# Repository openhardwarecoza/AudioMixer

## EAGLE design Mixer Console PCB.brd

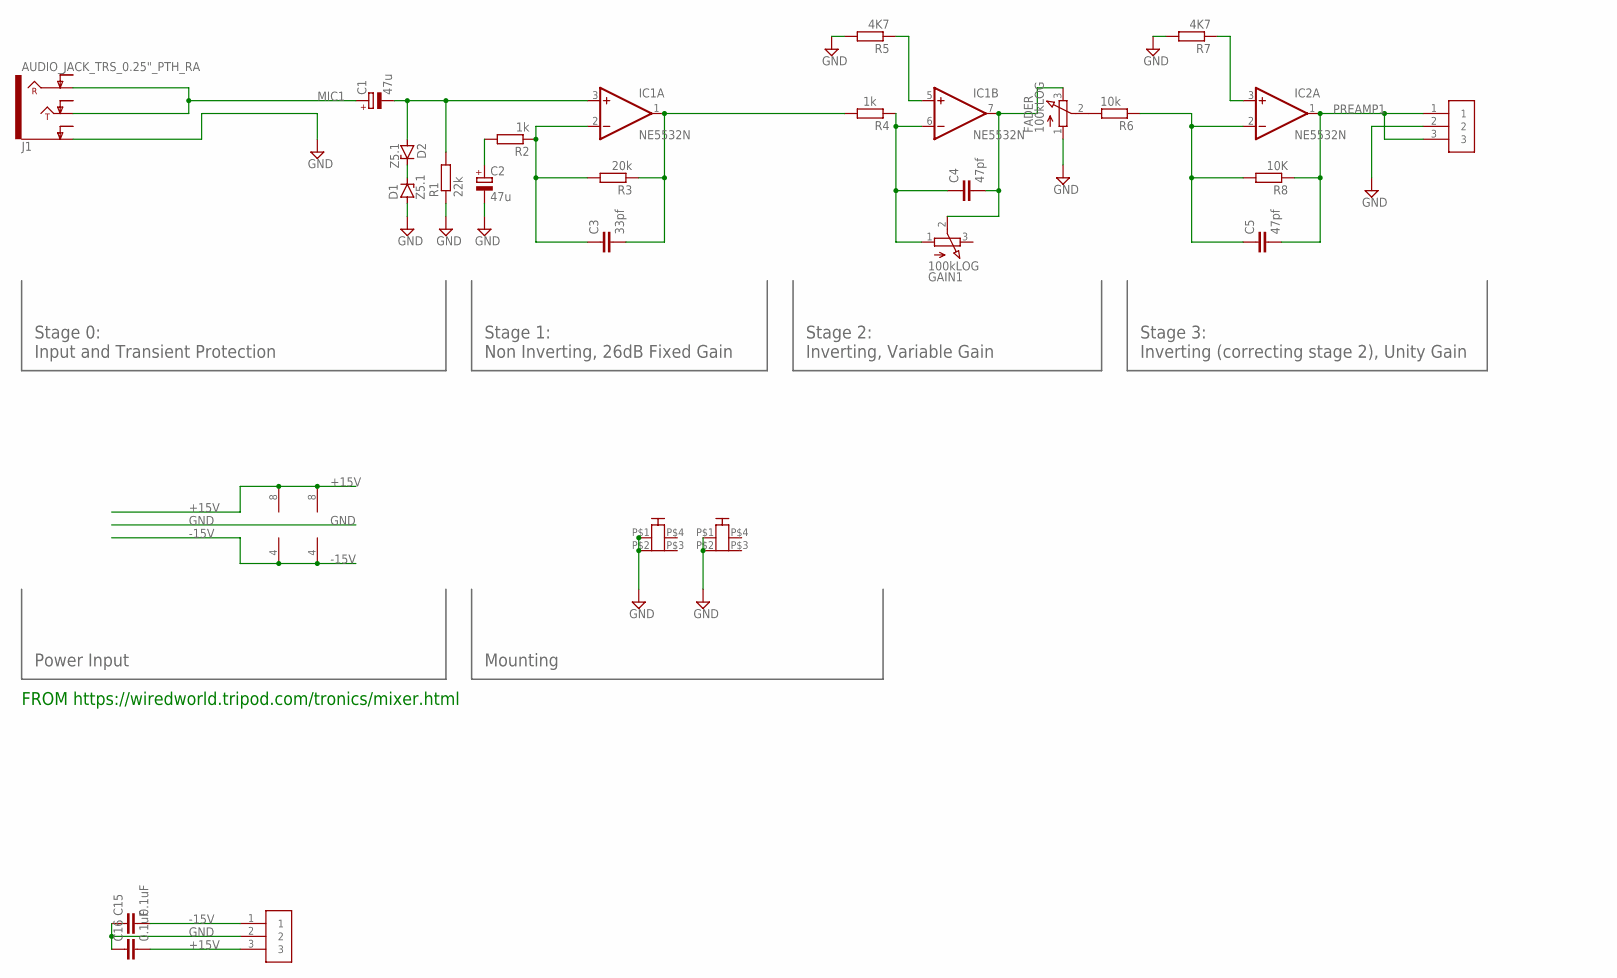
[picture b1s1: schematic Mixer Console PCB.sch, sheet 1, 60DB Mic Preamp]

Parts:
C1, C2: 47u; E5-6
C3: 33pf; C2.5-2
C4, C5: 47pf; C2.5-2
C15, C16: 0.1uF; C2.5-2
CON11, CON12: PCB-2M3; PCB2-M3
D1, D2: Z5.1; DO34Z7
FADER: 100kLOG; 3RP/1610N
GAIN1: 100kLOG; 3RP/1610N
IC1, IC2: NE5532N; DIL08
J1: AUDIO_JACK_TRS_0.25"_PTH_RA; AUDIO_JACK_0.25"_TRS_PTH_RA
PREAMPOUT: Phoenix Pluggable 3.81mm 3 way; 3.81MM-3WAY-PLUGGABLE-SCREW
PWRIN: Phoenix Pluggable 3.81mm 3 way; 3.81MM-3WAY-PLUGGABLE-SCREW
R1: 22k; 0204/7
R2, R4: 1k; 0204/7
R3: 20k; 0204/7
R5, R7: 4K7; 0204/7
R6: 10k; 0204/7
R8: 10K; 0204/7

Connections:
+15V: C16.2, IC1.8 (V+), IC2.8 (V+), PWRIN.3; also elsewhere on the board
-15V: C15.2, IC1.4 (V-), IC2.4 (V-), PWRIN.1; also elsewhere on the board
GND: C2.-, C15.1, C16.1, CON11.P$1, CON11.P$2, CON12.P$1, CON12.P$2, D1.A, FADER.1 (A), J1.SLEEVE (EARTH), PREAMPOUT.2, PWRIN.2, R1.1, R5.2, R7.2; also elsewhere on the board
MIC1: C1.+, J1.RING, J1.TIP
unnamed: C1.-, D2.A, IC1.3 (+IN), R1.2
unnamed: C2.+, R2.2
unnamed: C3.1, IC1.2 (-IN), R2.1, R3.2
unnamed: C3.2, IC1.1 (OUT), R3.1, R4.2
unnamed: C4.1, GAIN1.1 (A), IC1.6 (-IN), R4.1
unnamed: IC1.5 (+IN), R5.1
unnamed: C4.2, FADER.3 (E), GAIN1.2 (S), IC1.7 (OUT)
unnamed: IC2.3 (+IN), R7.1
unnamed: D1.C, D2.C
unnamed: C5.1, IC2.2 (-IN), R6.1, R8.2
unnamed: FADER.2 (S), R6.2
PREAMP1: C5.2, IC2.1 (OUT), PREAMPOUT.1, PREAMPOUT.3, R8.1

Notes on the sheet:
FROM https://wiredworld.tripod.com/tronics/mixer.html
Stage 1: Non Inverting, 26dB Fixed Gain
Stage 2: Inverting, Variable Gain
Stage 3: Inverting (correcting stage 2), Unity Gain
Stage 0: Input and Transient Protection
Power Input
Mounting

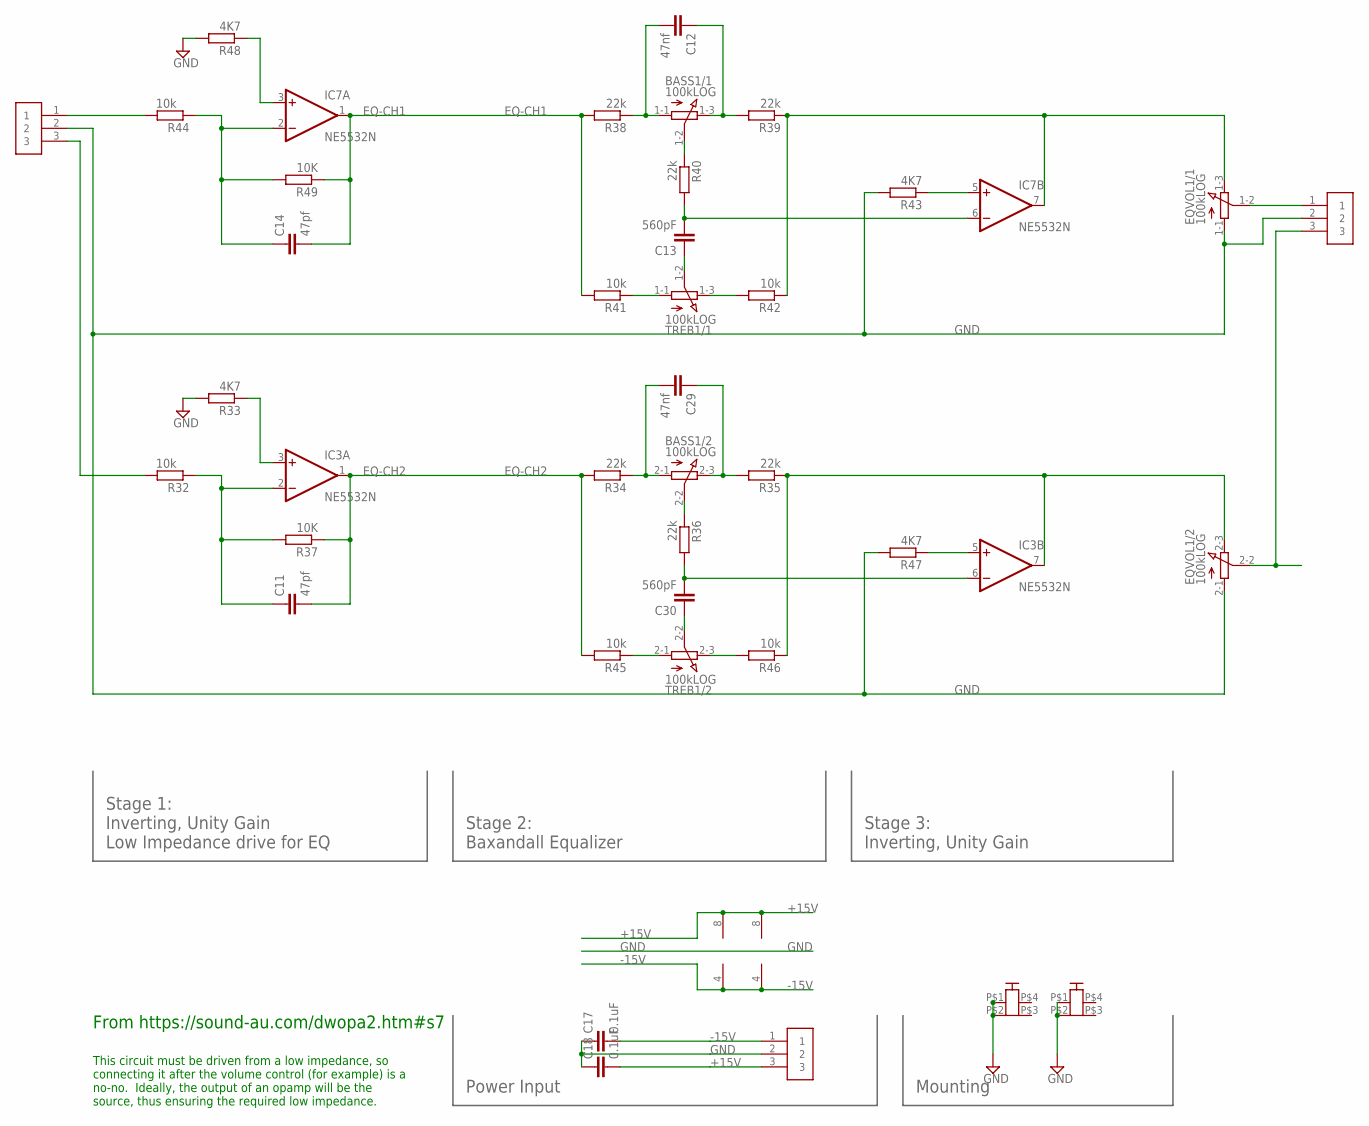
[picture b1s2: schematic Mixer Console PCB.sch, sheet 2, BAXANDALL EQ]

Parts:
BASS1: 100kLOG; 3RP/1610G
C11, C14: 47pf; C2.5-2
C12, C29: 47nf; C2.5-2
C13, C30: 560pF; C2.5-2
C17, C18: 0.1uF; C2.5-2
CON1, CON2: PCB-2M3; PCB2-M3
EQIN: Phoenix Pluggable 3.81mm 3 way; 3.81MM-3WAY-PLUGGABLE-SCREW
EQOUT: Phoenix Pluggable 3.81mm 3 way; 3.81MM-3WAY-PLUGGABLE-SCREW
EQVOL1: 100kLOG; 3RP/1610G
IC3, IC7: NE5532N; DIL08
PWRIN1: Phoenix Pluggable 3.81mm 3 way; 3.81MM-3WAY-PLUGGABLE-SCREW
R32, R41, R42, R44, R45, R46: 10k; 0204/7
R33, R43, R47, R48: 4K7; 0204/7
R34, R35, R36, R38, R39, R40: 22k; 0204/7
R37, R49: 10K; 0204/7
TREB1: 100kLOG; 3RP/1610G

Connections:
+15V: C18.2, IC3.8 (V+), IC7.8 (V+), PWRIN1.3; also elsewhere on the board
-15V: C17.2, IC3.4 (V-), IC7.4 (V-), PWRIN1.1; also elsewhere on the board
EQ-CH1: C14.2, IC7.1 (OUT), R38.2, R41.2, R49.1
EQ-CH2: C11.2, IC3.1 (OUT), R34.2, R37.1, R45.2
GND: C17.1, C18.1, CON1.P$1, CON1.P$2, CON2.P$1, CON2.P$2, EQIN.2, EQOUT.2, EQVOL1.1-1 (A), EQVOL1.2-1 (A), PWRIN1.2, R33.2, R43.2, R47.2, R48.2; also elsewhere on the board
unnamed: EQOUT.3, EQVOL1.2-2 (S)
unnamed: IC3.3 (+IN), R33.1
unnamed: C11.1, IC3.2 (-IN), R32.1, R37.2
unnamed: EQIN.3, R32.2
unnamed: BASS1.1-1 (A), C12.2, R38.1
unnamed: BASS1.1-3 (E), C12.1, R39.2
unnamed: BASS1.2-1 (A), C29.2, R34.1
unnamed: BASS1.2-3 (E), C29.1, R35.2
unnamed: BASS1.1-2 (S), R40.1
unnamed: BASS1.2-2 (S), R36.1
unnamed: C13.2, IC7.6 (-IN), R40.2
unnamed: C13.1, TREB1.1-2 (S)
unnamed: C30.2, IC3.6 (-IN), R36.2
unnamed: EQVOL1.1-3 (E), IC7.7 (OUT), R39.1, R42.1
unnamed: R42.2, TREB1.1-3 (E)
unnamed: C30.1, TREB1.2-2 (S)
unnamed: R41.1, TREB1.1-1 (A)
unnamed: IC7.5 (+IN), R43.1
unnamed: EQVOL1.2-3 (E), IC3.7 (OUT), R35.1, R46.1
unnamed: EQOUT.1, EQVOL1.1-2 (S)
unnamed: R46.2, TREB1.2-3 (E)
unnamed: R45.1, TREB1.2-1 (A)
unnamed: IC7.3 (+IN), R48.1
unnamed: C14.1, IC7.2 (-IN), R44.1, R49.2
unnamed: EQIN.1, R44.2
unnamed: IC3.5 (+IN), R47.1

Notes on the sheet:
Power Input
Mounting
Stage 2: Baxandall Equalizer
From https://sound-au.com/dwopa2.htm#s7
This circuit must be driven from a low impedance, so connecting it after the volume control (for example) is a no-no. Ideally, the output of an opamp will be the source, thus ensuring the required low impedance.
Stage 1: Inverting, Unity Gain Low Impedance drive for EQ
Stage 3: Inverting, Unity Gain

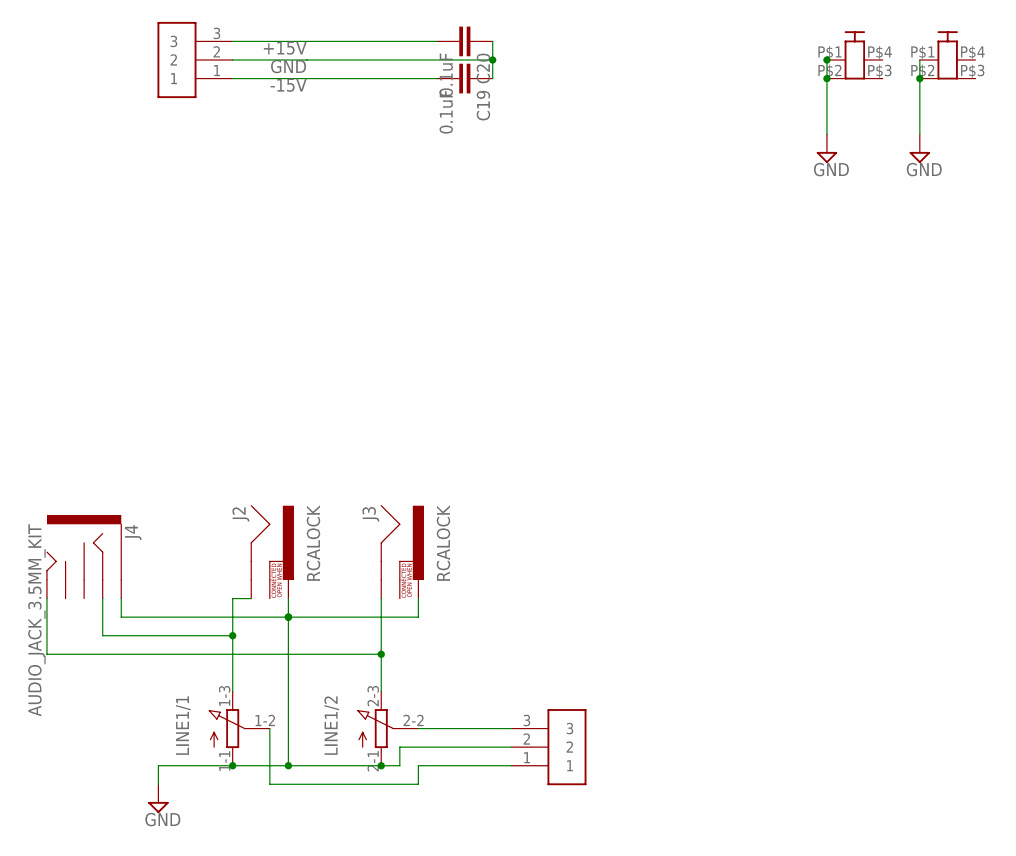
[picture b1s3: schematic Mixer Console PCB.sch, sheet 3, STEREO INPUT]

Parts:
C19, C20: 0.1uF; C2.5-2
CON3, CON4: PCB-2M3; PCB2-M3
J2, J3: RCALOCK; RCA_LOCK
J4: AUDIO_JACK_3.5MM_KIT; AUDIO-JACK-KIT
LINE1: 3RP/1610G
LINEIN-OUT: Phoenix Pluggable 3.81mm 3 way; 3.81MM-3WAY-PLUGGABLE-SCREW
PWRIN2: Phoenix Pluggable 3.81mm 3 way; 3.81MM-3WAY-PLUGGABLE-SCREW

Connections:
+15V: C20.2, PWRIN2.3; also elsewhere on the board
-15V: C19.2, PWRIN2.1; also elsewhere on the board
GND: C19.1, C20.1, CON3.P$1, CON3.P$2, CON4.P$1, CON4.P$2, J2.PIN, J3.PIN, J4.SLEEVE, LINE1.1-1 (A), LINE1.2-1 (A), LINEIN-OUT.2, PWRIN2.2; also elsewhere on the board
unnamed: LINE1.2-2 (S), LINEIN-OUT.3
unnamed: LINE1.1-2 (S), LINEIN-OUT.1
unnamed: J2.SHELL, J4.RING, LINE1.1-3 (E)
unnamed: J3.SHELL, J4.TIP, LINE1.2-3 (E)

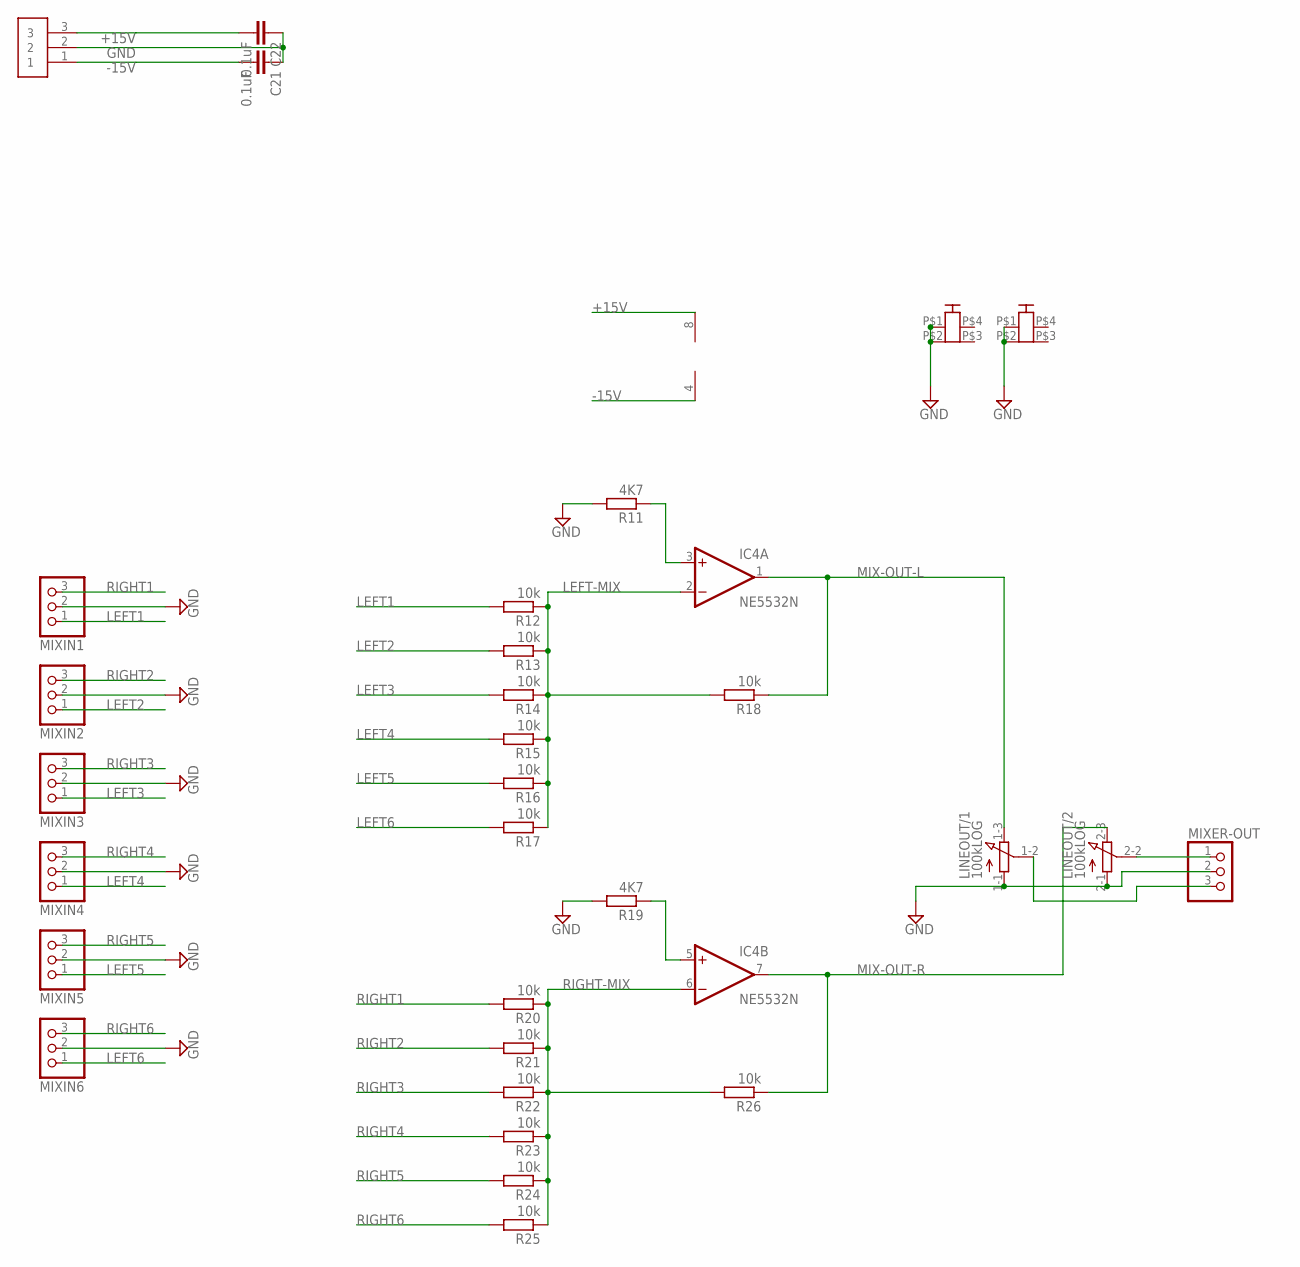
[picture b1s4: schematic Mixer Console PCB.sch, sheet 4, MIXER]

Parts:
C21, C22: 0.1uF; C2.5-2
CON5, CON6: PCB-2M3; PCB2-M3
IC4: NE5532N; DIL08
LINEOUT: 100kLOG; 3RP/1610G
MIXER-OUT: PINHD-1X3/90; 1X03/90
MIXIN1, MIXIN2, MIXIN3, MIXIN4, MIXIN5, MIXIN6: PINHD-1X3/90; 1X03/90
PWRIN3: Phoenix Pluggable 3.81mm 3 way; 3.81MM-3WAY-PLUGGABLE-SCREW
R11, R19: 4K7; 0204/7
R12, R13, R14, R15, R16, R17, R18, R20, R21, R22, R23, R24, R25, R26: 10k; 0204/7

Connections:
+15V: C22.2, IC4.8 (V+), PWRIN3.3; also elsewhere on the board
-15V: C21.2, IC4.4 (V-), PWRIN3.1; also elsewhere on the board
GND: C21.1, C22.1, CON5.P$1, CON5.P$2, CON6.P$1, CON6.P$2, LINEOUT.1-1 (A), LINEOUT.2-1 (A), MIXER-OUT.2, MIXIN1.2, MIXIN2.2, MIXIN3.2, MIXIN4.2, MIXIN5.2, MIXIN6.2, PWRIN3.2, R11.2, R19.2; also elsewhere on the board
LEFT1: MIXIN1.1, R12.2
LEFT2: MIXIN2.1, R13.2
LEFT3: MIXIN3.1, R14.2
LEFT4: MIXIN4.1, R15.2
LEFT5: MIXIN5.1, R16.2
LEFT6: MIXIN6.1, R17.2
LEFT-MIX: IC4.2 (-IN), R12.1, R13.1, R14.1, R15.1, R16.1, R17.1, R18.2
MIX-OUT-L: IC4.1 (OUT), LINEOUT.1-3 (E), R18.1
MIX-OUT-R: IC4.7 (OUT), LINEOUT.2-3 (E), R26.1
unnamed: IC4.5 (+IN), R19.1
unnamed: IC4.3 (+IN), R11.1
unnamed: LINEOUT.2-2 (S), MIXER-OUT.1
unnamed: LINEOUT.1-2 (S), MIXER-OUT.3
RIGHT1: MIXIN1.3, R20.2
RIGHT2: MIXIN2.3, R21.2
RIGHT3: MIXIN3.3, R22.2
RIGHT4: MIXIN4.3, R23.2
RIGHT5: MIXIN5.3, R24.2
RIGHT6: MIXIN6.3, R25.2
RIGHT-MIX: IC4.6 (-IN), R20.1, R21.1, R22.1, R23.1, R24.1, R25.1, R26.2

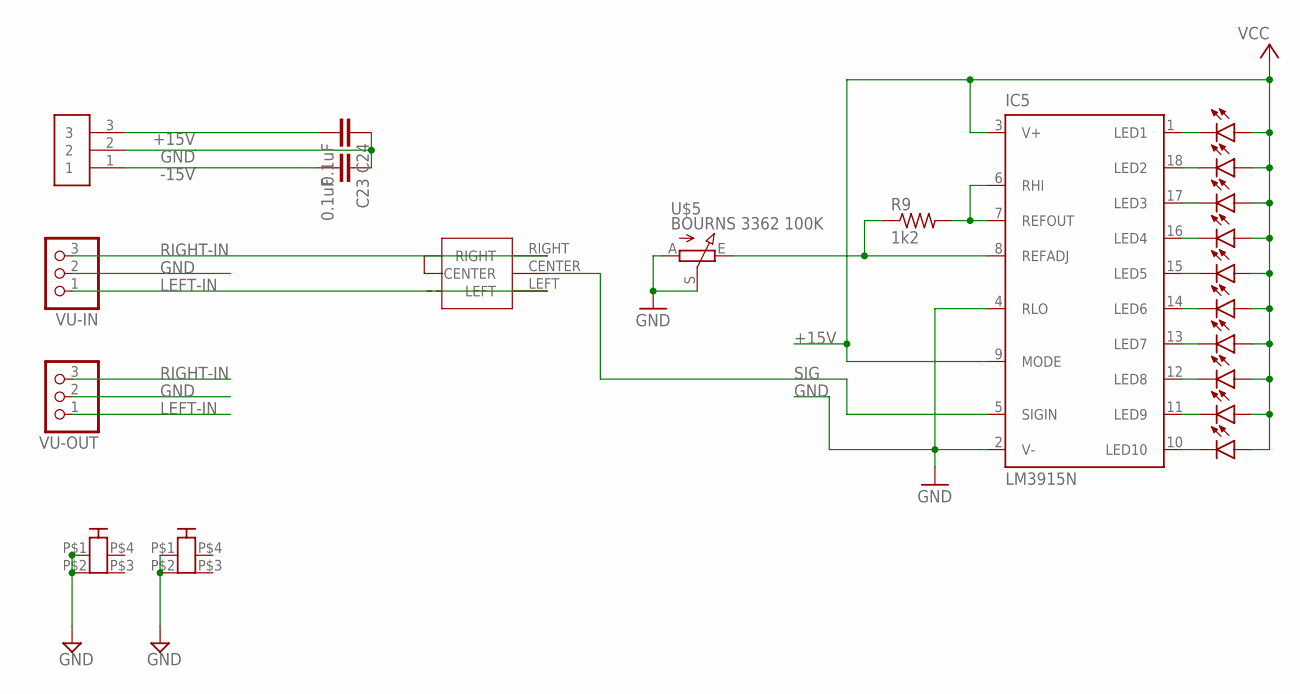
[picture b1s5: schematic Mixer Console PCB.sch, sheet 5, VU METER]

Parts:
C23, C24: 0.1uF; C2.5-2
CON7, CON8: PCB-2M3; PCB2-M3
IC5: LM3915N; DIL18
LED1, LED2, LED3, LED4, LED5, LED6, LED7, LED8, LED9, LED10: LED3MM
PWRIN4: Phoenix Pluggable 3.81mm 3 way; 3.81MM-3WAY-PLUGGABLE-SCREW
R9: 1k2; 0207/10
U$2: XKBENTERPRISESS-12D11G5R
U$5: BOURNS 3362 100K; POT_B64W
VU-IN: PINHD-1X3/90; 1X03/90
VU-OUT: PINHD-1X3/90; 1X03/90

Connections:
+15V: C24.2, IC5.3 (V+), IC5.9 (MODE), LED1.A, LED2.A, LED3.A, LED4.A, LED5.A, LED6.A, LED7.A, LED8.A, LED9.A, LED10.A, PWRIN4.3; also elsewhere on the board
-15V: C23.2, PWRIN4.1; also elsewhere on the board
GND: C23.1, C24.1, CON7.P$1, CON7.P$2, CON8.P$1, CON8.P$2, IC5.2 (V-), IC5.4 (RLO), PWRIN4.2, U$5.A, U$5.S, VU-IN.2, VU-OUT.2; also elsewhere on the board
LEFT-IN: U$2.LEFT, VU-IN.1, VU-OUT.1
unnamed: IC5.6 (RHI), IC5.7 (REFOUT), R9.2
unnamed: IC5.1 (LED1), LED1.K (C)
unnamed: IC5.18 (LED2), LED2.K (C)
unnamed: IC5.17 (LED3), LED3.K (C)
unnamed: IC5.16 (LED4), LED4.K (C)
unnamed: IC5.15 (LED5), LED5.K (C)
unnamed: IC5.14 (LED6), LED6.K (C)
unnamed: IC5.13 (LED7), LED7.K (C)
unnamed: IC5.12 (LED8), LED8.K (C)
unnamed: IC5.11 (LED9), LED9.K (C)
unnamed: IC5.10 (LED10), LED10.K (C)
REF: IC5.8 (REFADJ), R9.1, U$5.E
RIGHT-IN: U$2.RIGHT, VU-IN.3, VU-OUT.3
SIG: IC5.5 (SIGIN), U$2.CENTER

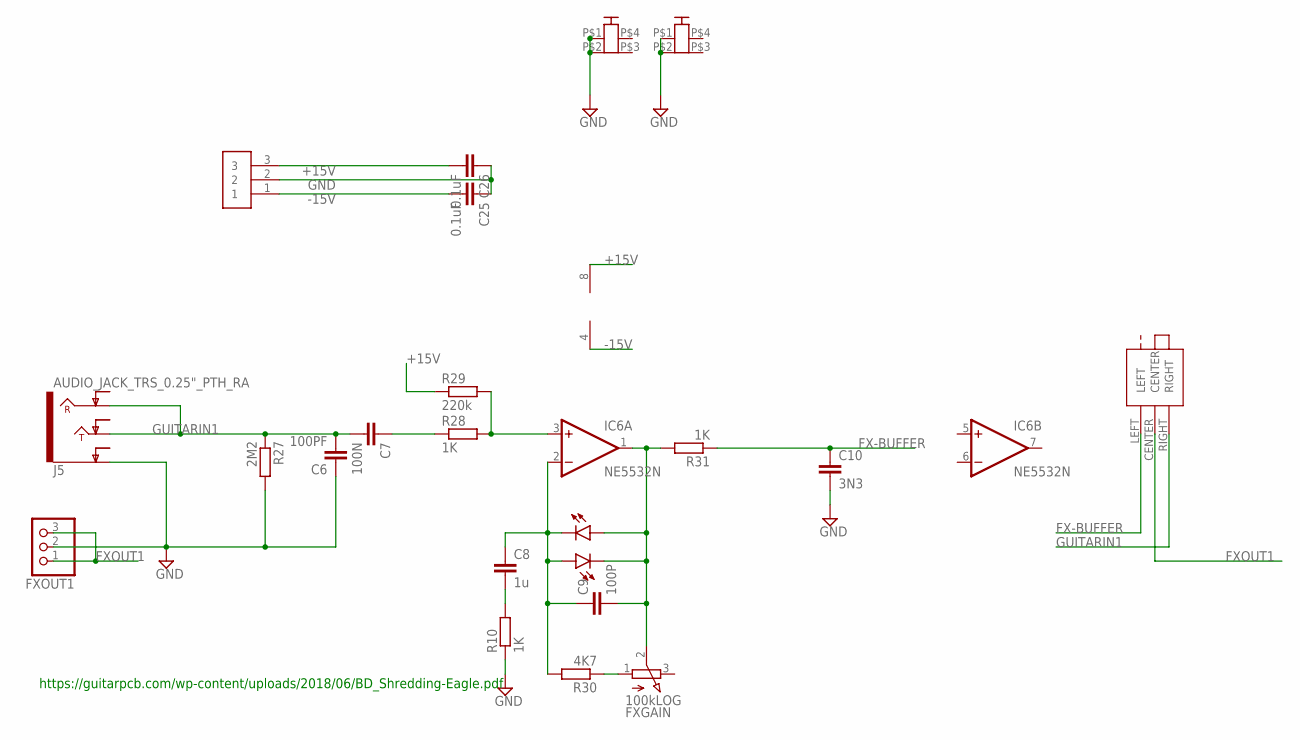
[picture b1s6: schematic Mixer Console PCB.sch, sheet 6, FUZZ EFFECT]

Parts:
C6: 100PF; C2.5-2
C7: 100N; C2.5-2
C8: 1u; C2.5-2
C9: 100P; C2.5-2
C10: 3N3; C2.5-2
C25, C26: 0.1uF; C2.5-2
CON9, CON10: PCB-2M3; PCB2-M3
FXGAIN: 100kLOG; 3RP/1610N
FXOUT1: PINHD-1X3/90; 1X03/90
IC6: NE5532N; DIL08
J5: AUDIO_JACK_TRS_0.25"_PTH_RA; AUDIO_JACK_0.25"_TRS_PTH_RA
LED11, LED12: LED3MM
PWRIN5: Phoenix Pluggable 3.81mm 3 way; 3.81MM-3WAY-PLUGGABLE-SCREW
R10, R28, R31: 1K; 0204/7
R27: 2M2; 0204/7
R29: 220k; 0204/7
R30: 4K7; 0204/7
U$1: XKBENTERPRISESS-12D11G5R

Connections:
+15V: C26.2, IC6.8 (V+), PWRIN5.3, R29.1; also elsewhere on the board
-15V: C25.2, IC6.4 (V-), PWRIN5.1; also elsewhere on the board
FX-BUFFER: C10.1, R31.1, U$1.LEFT
FXOUT1: FXOUT1.1, FXOUT1.3, U$1.CENTER
GND: C6.1, C10.2, C25.1, C26.1, CON9.P$1, CON9.P$2, CON10.P$1, CON10.P$2, FXOUT1.2, J5.SLEEVE (EARTH), PWRIN5.2, R10.1, R27.2; also elsewhere on the board
GUITARIN1: C6.2, C7.2, J5.RING, J5.TIP, R27.1, U$1.RIGHT
unnamed: IC6.3 (+IN), R28.2, R29.2
unnamed: C7.1, R28.1
unnamed: C8.1, C9.1, IC6.2 (-IN), LED11.K (C), LED12.A, R30.2
unnamed: C9.2, FXGAIN.2 (S), IC6.1 (OUT), LED11.A, LED12.K (C), R31.2
unnamed: C8.2, R10.2
unnamed: FXGAIN.1 (A), R30.1

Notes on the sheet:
https://guitarpcb.com/wp-content/uploads/2018/06/BD_Shredding-Eagle.pdf

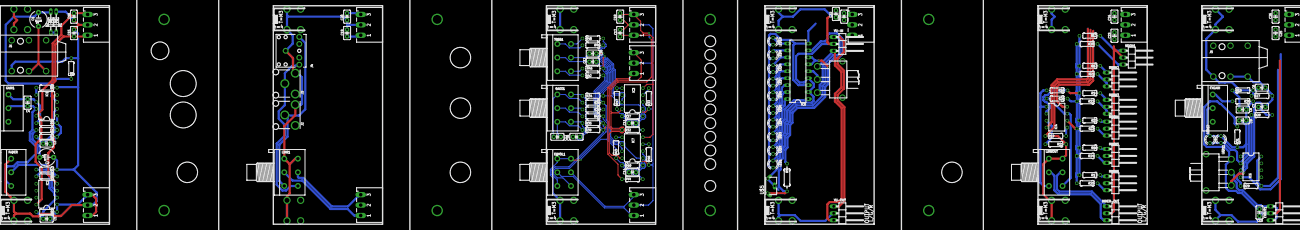
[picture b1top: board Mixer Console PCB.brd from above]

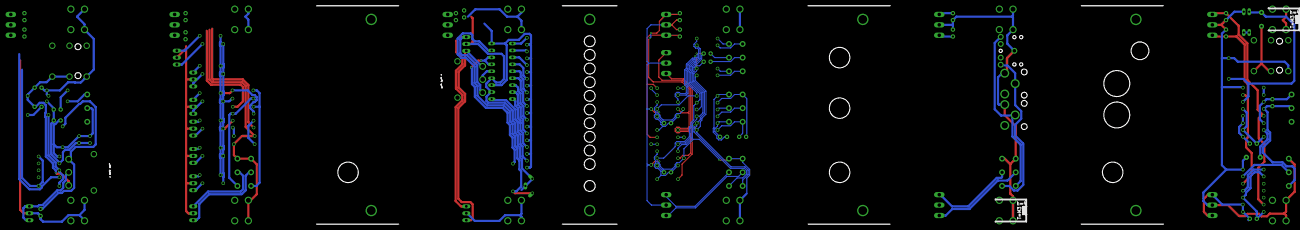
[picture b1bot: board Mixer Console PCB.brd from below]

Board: 2 copper layers, 146 parts (2 on the bottom side), 92 nets.

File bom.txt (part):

Partlist

Exported from Mixer Console PCB.brd at 2021/04/04 20:23

EAGLE Version 9.6.2 Copyright (c) 1988-2020 Autodesk, Inc.

Assembly variant: 

Part       Value                       Package                     Library                    Position (mm)         Orientation

BASS1      100kLOG                     3RP/1610G                   pot                        (124 42.5)            R270
C1         47u                         E5-6                        rcl                        (14 75)               R90
C2         47u                         E5-6                        rcl                        (17 24.5)             R0
C3         33pf                        C2.5-2                      capacitor-wima             (17 29.5)             R0
C4         47pf                        C2.5-2                      capacitor-wima             (10 44.5)             R270
C5         47pf                        C2.5-2                      capacitor-wima             (17 2)                R0
C6         100PF                       C2.5-2                      capacitor-wima             (322 50)              R0
C7         100N                        C2.5-2                      capacitor-wima             (322 43)              R0
C8         1u                          C2.5-2                      capacitor-wima             (315 42)              R180
C9         100P                        C2.5-2                      capacitor-wima             (315 38)              R180
C10        3N3                         C2.5-2                      capacitor-wima             (321.1 4.3)           R270
C11        47pf                        C2.5-2                      capacitor-wima             (151.5 46)            R0
C12        47nf                        C2.5-2                      capacitor-wima             (124 32)              R180
C13        560pF                       C2.5-2                      capacitor-wima             (137 59.5)            R0
C14        47pf                        C2.5-2                      capacitor-wima             (151.5 28)            R0
C29        47nf                        C2.5-2                      capacitor-wima             (131 32)              R180
C30        560pF                       C2.5-2                      capacitor-wima             (137 62.5)            R0
CON1       PCB-2M3                     PCB2-M3                     Screw Terminals            (60 75)               R90
CON2       PCB-2M3                     PCB2-M3                     Screw Terminals            (60 5)                MR270
CON3       PCB-2M3                     PCB2-M3                     Screw Terminals            (120 75)              R90
CON4       PCB-2M3                     PCB2-M3                     Screw Terminals            (120 5)               R90
CON5       PCB-2M3                     PCB2-M3                     Screw Terminals            (180 75)              R90
CON6       PCB-2M3                     PCB2-M3                     Screw Terminals            (180 5)               R90
CON7       PCB-2M3                     PCB2-M3                     Screw Terminals            (240 75)              R90
CON8       PCB-2M3                     PCB2-M3                     Screw Terminals            (240 5)               R90
CON9       PCB-2M3                     PCB2-M3                     Screw Terminals            (300 75)              R90
CON10      PCB-2M3                     PCB2-M3                     Screw Terminals            (300 5)               R90
CON11      PCB-2M3                     PCB2-M3                     Screw Terminals            (0 5)                 R90
CON12      PCB-2M3                     PCB2-M3                     Screw Terminals            (0 75)                MR270
D1         Z5.1                        DO34Z7                      diode                      (20.5 74)             R90
D2         Z5.1                        DO34Z7                      diode                      (18.5 74)             R90
EQIN2                                  1X03/90                     pinhead                    (149 66)              R270
EQOUT2                                 1X03/90                     pinhead                    (149 4)               R270
EQVOL1     100kLOG                     3RP/1610G                   pot                        (124 19)              R270
FADER      100kLOG                     3RP/1610N                   pot                        (4 19)                R270
FXGAIN     100kLOG                     3RP/1610N                   pot                        (304 42.5)            R270
FXOUT1                                 1X03/90                     pinhead                    (329 4)               R270
GAIN1      100kLOG                     3RP/1610N                   pot                        (3 42.5)              R270
IC1        NE5532N                     DIL08                       linear                     (17 43.5)             R90
IC2        NE5532N                     DIL08                       linear                     (17 11)               R90
IC3        NE5532N                     DIL08                       linear                     (151.5 55)            R90
IC4        NE5532N                     DIL08                       linear                     (246.9 39.2)          R270
IC5        LM3915N                     DIL18                       national-semiconductor     (192.1 56)            R90
IC6        NE5532N                     DIL08                       linear                     (318 21)              R270
IC7        NE5532N                     DIL08                       linear                     (151.5 37)            R90
J1         AUDIO_JACK_TRS_0.25"_PTH_RA AUDIO_JACK_0.25"_TRS_PTH_RA SparkFun-Connectors        (0 61)                R0
J2         RCALOCK                     RCA_LOCK                    SparkFun-Connectors        (64 40)               R0
J3         RCALOCK                     RCA_LOCK                    SparkFun-Connectors        (64 51.5)             R0
J4         AUDIO_JACK_3.5MM_KIT        AUDIO-JACK-KIT              SparkFun-Connectors        (64.5 63.5)           R0
J5         AUDIO_JACK_TRS_0.25"_PTH_RA AUDIO_JACK_0.25"_TRS_PTH_RA SparkFun-Connectors        (300 61)              R0
LED1                                   LED3MM                      led                        (183 22)              R90
LED2                                   LED3MM                      led                        (183 27)              R90
LED3                                   LED3MM                      led                        (183 32)              R90
LED4                                   LED3MM                      led                        (183 37)              R90
LED5                                   LED3MM                      led                        (183 42)              R90
LED6                                   LED3MM                      led                        (183 47)              R90
LED7                                   LED3MM                      led                        (183 52)              R90
LED8                                   LED3MM                      led                        (183 57)              R90
LED9                                   LED3MM                      led                        (183 62)              R90
LED10                                  LED3MM                      led                        (183 67)              R90
LED11                                  LED3MM                      led                        (307 31)              R270
LED12                                  LED3MM                      led                        (303 31)              R90
LINE1                                  3RP/1610G                   pot                        (64 19)               R270
LINEOUT    100kLOG                     3RP/1610G                   pot                        (244 19)              R270
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
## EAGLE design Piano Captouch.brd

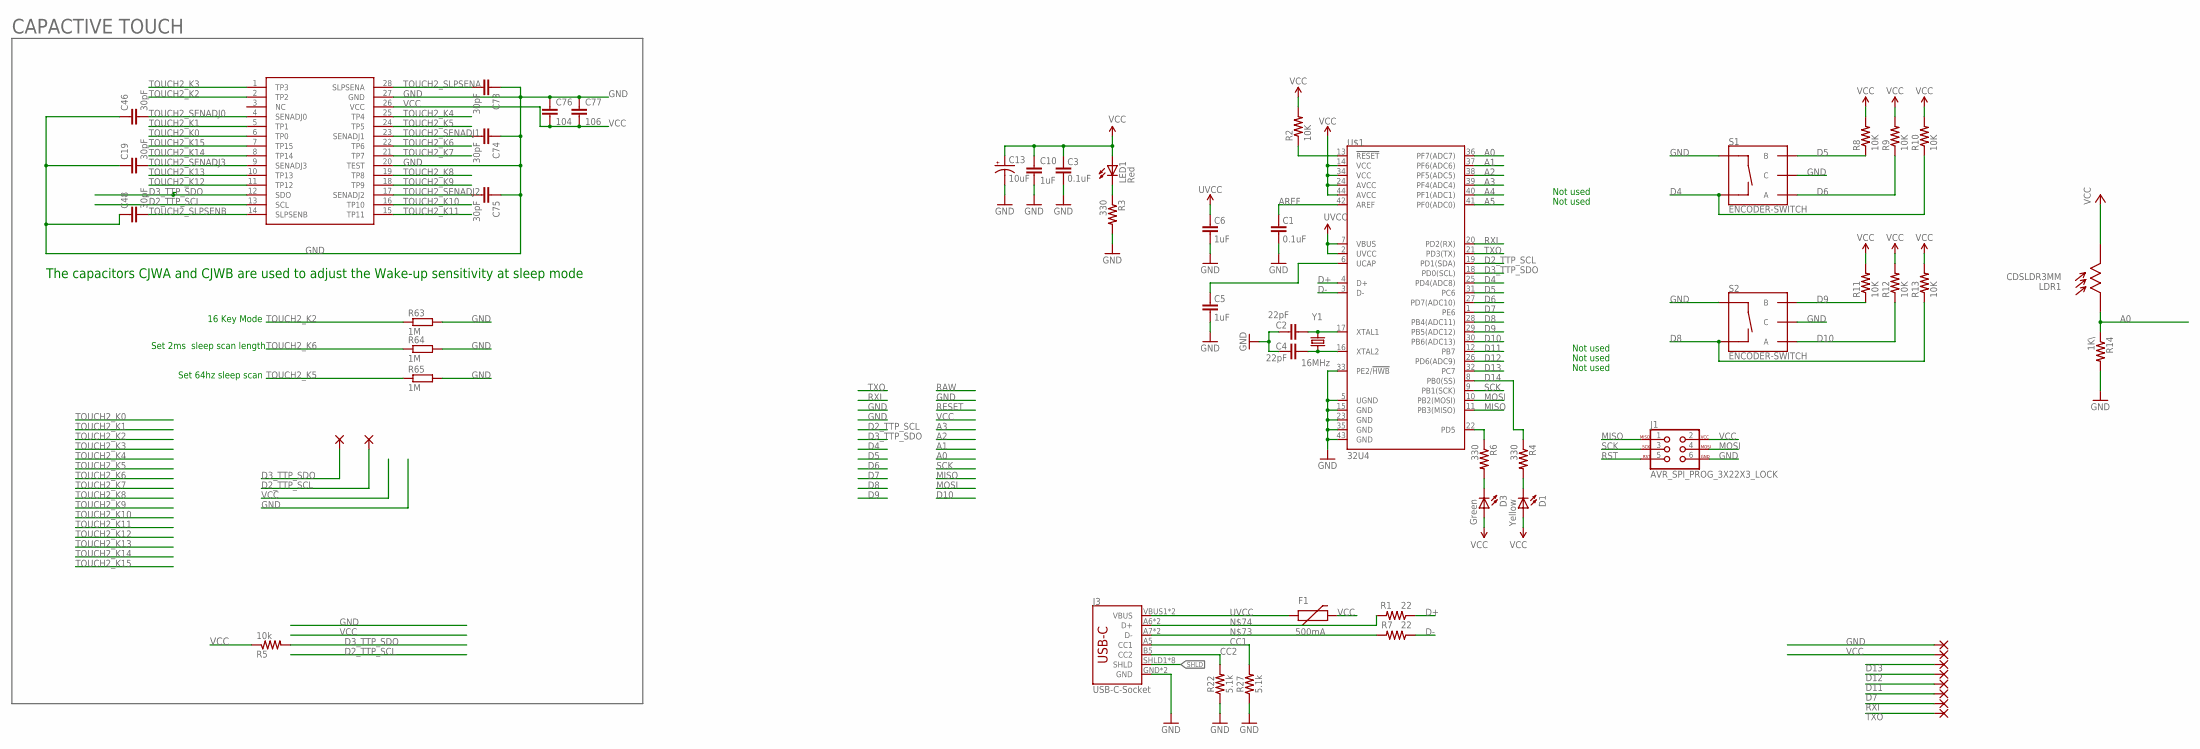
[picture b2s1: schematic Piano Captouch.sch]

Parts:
C1, C3: 0.1uF; 0603-CAP
C2, C4: 22pF; 0603-CAP
C5, C10: 1uF; 0805
C6: 1uF; 0603-CAP
C13: 10uF; EIA3216
C19, C46, C48, C73, C74, C75: 30pF; C0603K
C76: 104; C0603K
C77: 106; C1206
D1: Yellow; LED-0603
D3: Green; LED-0603
F1: 500mA; PTC-1206
IC1: TTP229; TTP229-SSOP28
J1: AVR_SPI_PROG_3X22X3_LOCK; 2X3_LOCK
J3: USB-C-Socket; USB-C-16P
LDR1: CDSLDR3MM; LDR3MM
LED1: Red; LED-0603
PAD1, PAD2, PAD3, PAD4, PAD5, PAD6, PAD7, PAD8, PAD9, PAD10: 2,15/1,0
R1, R7: 22; 0603-RES
R2, R8, R9, R10, R11, R12, R13: 10K; 0603-RES
R3, R4, R6: 330; 0603-RES
R5: 10k; R0603
R14: 1K\; 0603-RES
R22, R27: 5.1k; 0603@1
R63, R64, R65: 1M; R0603
S1, S2: ENCODER-SWITCH; ROTARY_ENC_PLAIN
U$1: 32U4; TQFP44
Y1: 16MHz; HC49U-V

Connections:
A0: LDR1.P$1, R14.1, U$1.36 (PF7(ADC7))
A1: U$1.37 (PF6(ADC6))
A2: U$1.38 (PF5(ADC5))
A3: U$1.39 (PF4(ADC4))
A4: U$1.40 (PF1(ADC1))
A5: U$1.41 (PF0(ADC0))
AREF: C1.2, U$1.42 (AREF)
CC1: J3.A5 (CC1), R27.2
CC2: J3.B5 (CC2), R22.2
D2_TTP_SCL: IC1.13 (SCL), PAD10.1, U$1.19 (PD1(SDA))
D3_TTP_SDO: IC1.12 (SDO), PAD9.1, R5.2, U$1.18 (PD0(SCL))
D4: R10.1, S1.SW-, U$1.25 (PD4(ADC8))
D5: R8.1, S1.B, U$1.31 (PC6)
D6: R9.1, S1.A, U$1.27 (PD7(ADC10))
D7: PAD4.1, U$1.1 (PE6)
D8: R13.1, S2.SW-, U$1.28 (PB4(ADC11))
D9: R11.1, S2.B, U$1.29 (PB5(ADC12))
D10: R12.1, S2.A, U$1.30 (PB6(ADC13))
D11: PAD3.1, U$1.12 (PB7)
D12: PAD2.1, U$1.26 (PD6(ADC9))
D13: PAD1.1, U$1.32 (PC7)
D14: R4.1, U$1.8 (PB0(SS))
D+: R1.1, U$1.4 (D+)
D-: R7.1, U$1.3 (D-)
GND: C1.1, C2.2, C3.1, C4.2, C5.1, C6.1, C10.2, C13.C (-), C19.1, C46.1, C48.1, C73.1, C74.1, C75.1, C76.1, C77.1, IC1.20 (TEST), IC1.27 (GND), J1.6, J3.GND, J3.GND2 (GND), PAD8.1, R3.2, R14.2, R22.1, R27.1, R63.2, R64.2, R65.2, S1.C, S1.SW+, S2.C, S2.SW+, U$1.5 (UGND), U$1.15 (GND), U$1.23 (GND), U$1.33 (PE2/!HWB), U$1.35 (GND), U$1.43 (GND)
MISO: J1.1, U$1.11 (PB3(MISO))
MOSI: J1.4, U$1.10 (PB2(MOSI))
unnamed: LED1.C, R3.1
unnamed: C4.1, U$1.16 (XTAL2), Y1.1
unnamed: C2.1, U$1.17 (XTAL1), Y1.2
unnamed: C5.2, U$1.6 (UCAP)
unnamed: J3.A7 (D-), J3.B7 (D-), R7.2
unnamed: J3.A6 (D+), J3.B6 (D+), R1.2
unnamed: D1.C, R4.2
unnamed: D3.C, R6.2
RESET: R2.1, U$1.13 (!RESET)
RST: J1.5
RXI: PAD5.1, U$1.20 (PD2(RX))
SCK: J1.3, U$1.9 (PB1(SCK))
SHLD: J3.SHLD1 (SHLD), J3.SHLD2 (SHLD), J3.SHLD3 (SHLD), J3.SHLD4 (SHLD), J3.SHLD5 (SHLD), J3.SHLD6 (SHLD), J3.SHLD7 (SHLD), J3.SHLD8 (SHLD)
TOUCH2_K0: IC1.6 (TP0)
TOUCH2_K1: IC1.5 (TP1)
TOUCH2_K2: IC1.2 (TP2), R63.1
TOUCH2_K3: IC1.1 (TP3)
TOUCH2_K4: IC1.25 (TP4)
TOUCH2_K5: IC1.24 (TP5), R65.1
TOUCH2_K6: IC1.22 (TP6), R64.1
TOUCH2_K7: IC1.21 (TP7)
TOUCH2_K8: IC1.19 (TP8)
TOUCH2_K9: IC1.18 (TP9)
TOUCH2_K10: IC1.16 (TP10)
TOUCH2_K11: IC1.15 (TP11)
TOUCH2_K12: IC1.11 (TP12)
TOUCH2_K13: IC1.10 (TP13)
TOUCH2_K14: IC1.8 (TP14)
TOUCH2_K15: IC1.7 (TP15)
TOUCH2_SENADJ0: C46.2, IC1.4 (SENADJ0)
TOUCH2_SENADJ1: C74.2, IC1.23 (SENADJ1)
TOUCH2_SENADJ2: C75.2, IC1.17 (SENADJ2)
TOUCH2_SENADJ3: C19.2, IC1.9 (SENADJ3)
TOUCH2_SLPSENA: C73.2, IC1.28 (SLPSENA)
TOUCH2_SLPSENB: C48.2, IC1.14 (SLPSENB)
TXLED: R6.1, U$1.22 (PD5)
TXO: PAD6.1, U$1.21 (PD3(TX))
UVCC: C6.2, F1.1, J3.VBUS1 (VBUS), J3.VBUS2 (VBUS), U$1.2 (UVCC), U$1.7 (VBUS)
VCC: C3.2, C10.1, C13.A (+), C76.2, C77.2, D1.A, D3.A, F1.2, IC1.26 (VCC), J1.2, LDR1.P$2, LED1.A, PAD7.1, R2.2, R5.1, R8.2, R9.2, R10.2, R11.2, R12.2, R13.2, U$1.14 (VCC), U$1.24 (AVCC), U$1.34 (VCC), U$1.44 (AVCC)

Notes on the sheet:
CAPACTIVE TOUCH
Set 2ms sleep scan length
16 Key Mode
Set 64hz sleep scan
The capacitors CJWA and CJWB are used to adjust the Wake-up sensitivity at sleep mode
Not used

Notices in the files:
parts and their libraries:
SparkFun-Connectors: Licensing: Creative Commons ShareAlike 4.0 International - https://creativecommons.org/licenses/by-sa/4.0
SparkFun-Resistors: Licensing: CC v3.0 Share-Alike You are welcome to use this library for commercial purposes.
SparkFun-Aesthetics: Released under the Creative Commons
